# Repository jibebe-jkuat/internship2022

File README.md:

# EV project internship 2022

[PPT Slide](https://docs.google.com/presentation/d/1OYJdxiVj7QEA71lRJihHxvrTG2KooOGciBFLIxmFiqk/edit?usp=sharing)

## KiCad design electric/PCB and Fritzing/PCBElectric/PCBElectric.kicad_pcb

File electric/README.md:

# System Specifications

# MOTOR
Motor: BLDC <BR>
Voltage: 48V <br>
Power rating: 1200W <br>
Serial No: TP48V 1200W H60 210918 0001 <br>

# Speed Controller

Voltage : 48V
Power rating: 1200W

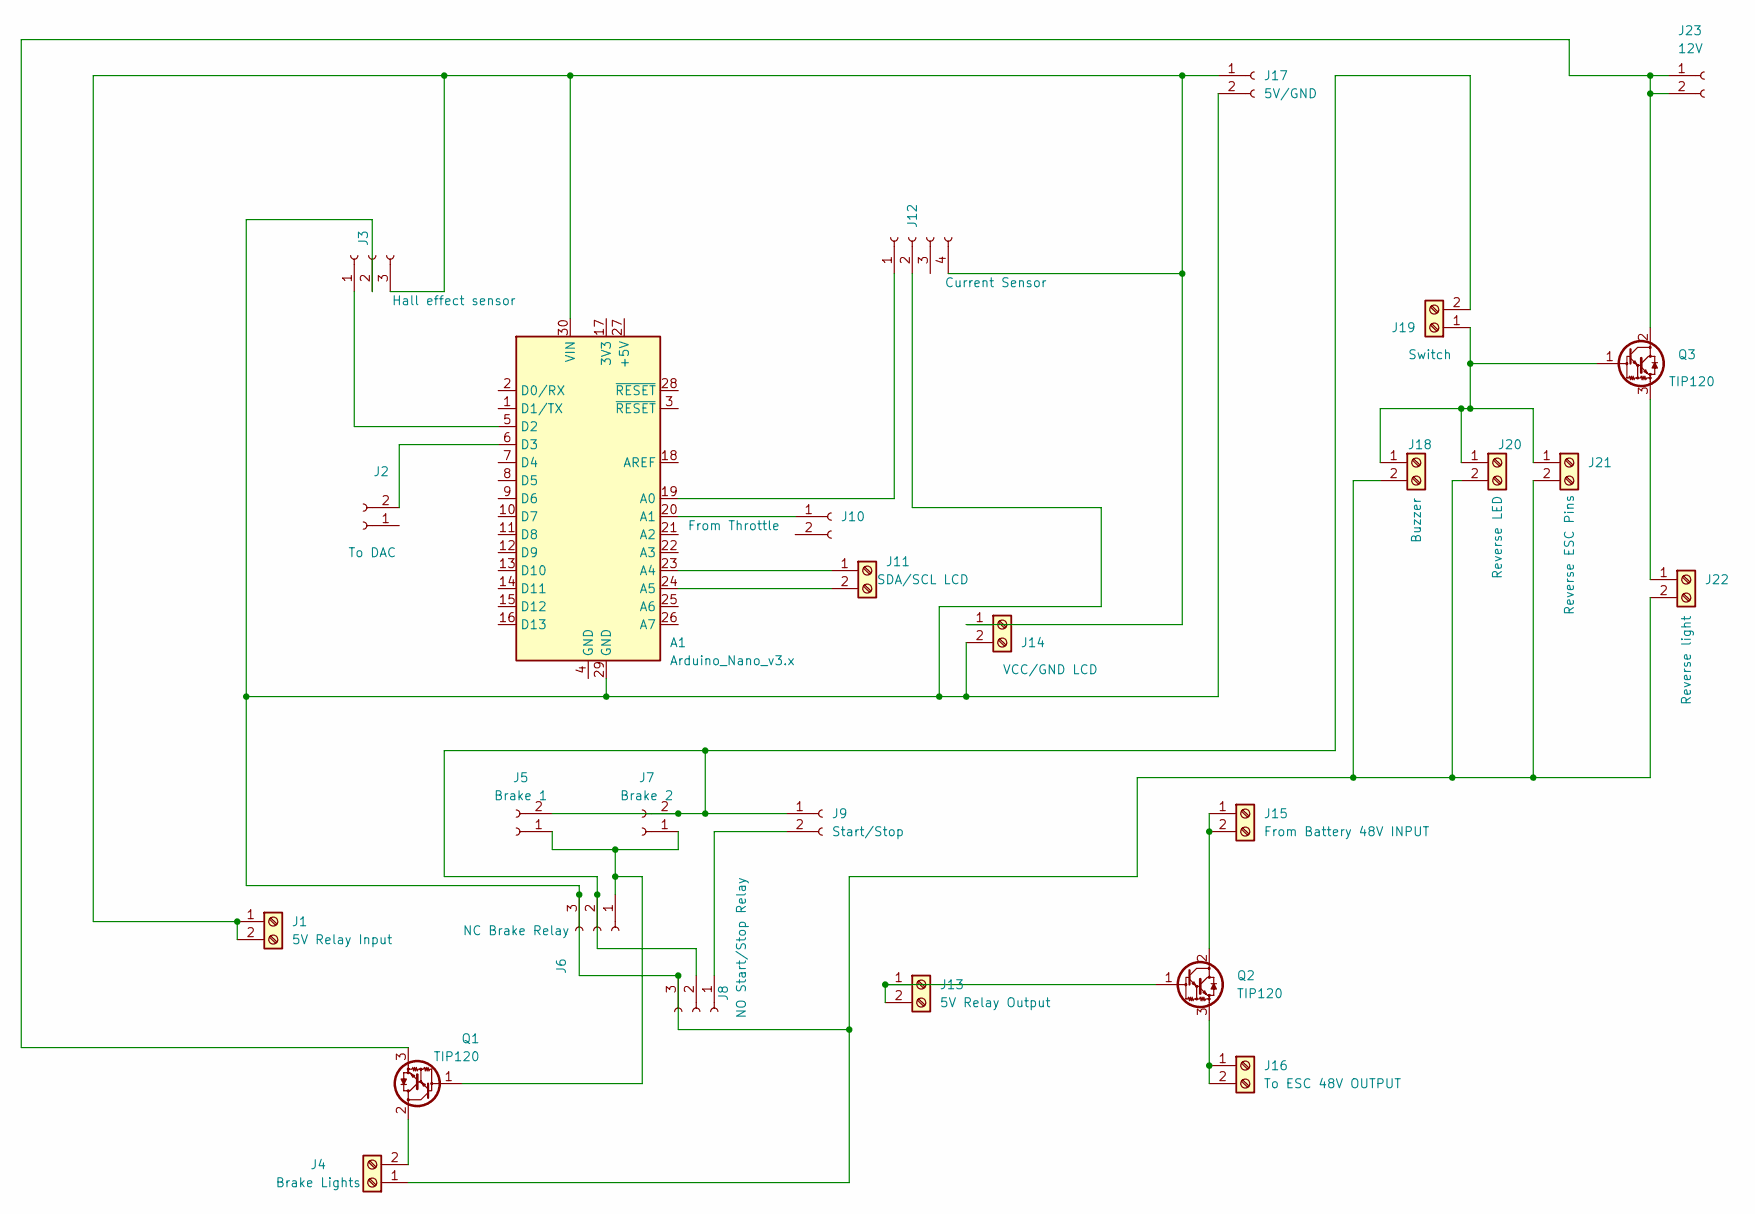
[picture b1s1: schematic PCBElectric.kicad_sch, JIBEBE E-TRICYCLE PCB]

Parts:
A1: Arduino_Nano_v3.x; Arduino_Nano
J1: 5V Relay Input; TerminalBlock_Altech_AK300-2_P5.00mm
J2: To DAC; PinHeader_1x02_P2.54mm_Vertical
J3: Hall effect sensor; PinSocket_1x03_P2.54mm_Vertical
J4: Brake Lights; TerminalBlock_Altech_AK300-2_P5.00mm
J5: Brake 1; PinSocket_1x02_P2.54mm_Vertical
J6: NC Brake Relay; PinSocket_1x03_P2.54mm_Vertical
J7: Brake 2; PinSocket_1x02_P2.54mm_Vertical
J8: NO Start/Stop Relay; PinSocket_1x03_P2.54mm_Vertical
J9: Start/Stop; PinSocket_1x02_P2.54mm_Vertical
J10: From Throttle; PinHeader_1x02_P2.54mm_Vertical
J11: SDA/SCL LCD; TerminalBlock_Altech_AK300-2_P5.00mm
J12: Current Sensor; PinSocket_1x04_P2.54mm_Vertical
J13: 5V Relay Output; TerminalBlock_Altech_AK300-2_P5.00mm
J14: VCC/GND LCD; TerminalBlock_Altech_AK300-2_P5.00mm
J15: From Battery 48V INPUT; TerminalBlock_Altech_AK300-2_P5.00mm
J16: To ESC 48V OUTPUT; TerminalBlock_Altech_AK300-2_P5.00mm
J17: 5V/GND; PinHeader_1x02_P2.54mm_Vertical
J18: Buzzer; TerminalBlock_Altech_AK300-2_P5.00mm
J19: Switch; TerminalBlock_Altech_AK300-2_P5.00mm
J20: Reverse LED; TerminalBlock_Altech_AK300-2_P5.00mm
J21: Reverse ESC Pins; TerminalBlock_Altech_AK300-2_P5.00mm
J22: Reverse light; TerminalBlock_Altech_AK300-2_P5.00mm
J23: 12V; PinHeader_1x02_P2.54mm_Vertical
Q1, Q2, Q3: TIP120; TO-220-3_Vertical

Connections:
unnamed: A1.5 (D2), J3.1
unnamed: A1.6 (D3), J2.2
unnamed: A1.19 (A0), J12.1
unnamed: A1.20 (A1), J10.1
unnamed: A1.23 (A4), J11.1
unnamed: A1.24 (A5), J11.2
unnamed: A1.29 (GND), J3.2, J4.1, J6.3, J8.3, J12.2, J14.2, J17.2, J18.2, J20.2, J21.2, J22.2
unnamed: A1.30 (VIN), J1.1, J1.2, J3.3, J12.4, J14.1, J17.1
unnamed: J4.2, Q1.2 (C)
unnamed: J5.1, J6.1, J7.1, Q1.1 (B)
unnamed: J8.1, J9.2
unnamed: J13.1, J13.2, Q2.1 (B)
unnamed: J15.1, J15.2, Q2.2 (C)
unnamed: J16.1, J16.2, Q2.3 (E)
unnamed: J18.1, J19.1, J20.1, J21.1, Q3.1 (B)
unnamed: J5.2, J6.2, J7.2, J8.2, J9.1, J19.2
unnamed: J22.1, Q3.3 (E)
unnamed: J23.1, J23.2, Q1.3 (E), Q3.2 (C)

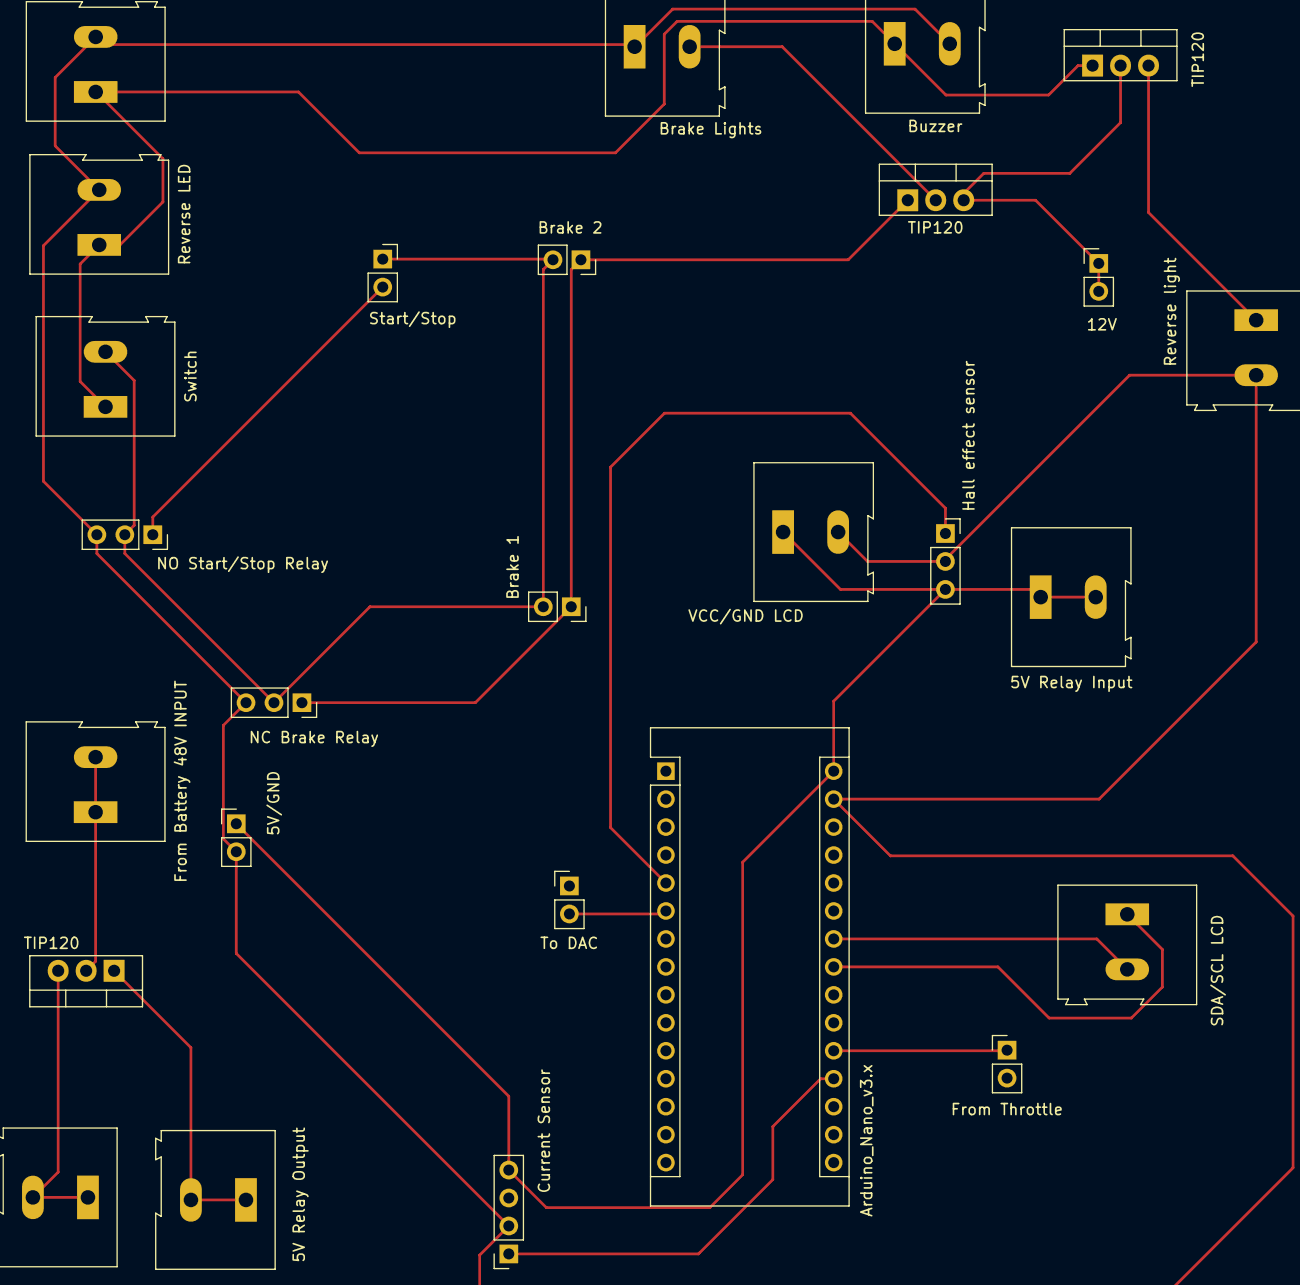
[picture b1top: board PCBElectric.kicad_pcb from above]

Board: 2 copper layers, 27 parts (0 on the bottom side), 18 nets.

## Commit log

2022-01-13 add students
2022-01-13 add introduction slide on readme
2022-01-13 Updated layout of electric team folder
    Different subdirectories have been created to match expected goals
2022-01-14 Uploaded Schematic For Speed Control
2022-01-14 Uploaded README's for the subdirectories
2022-01-16 Uploaded pdf containing choice of battery
2022-01-16 Uploaded code and schematic for speed control
2022-01-17 uploaded battery selection program
2022-01-17 CREATED TXT
2022-01-17 tractor robot chassis
2022-01-17 PARTS USED IN MAKING A OBSTACLE AVOIDING ROBOT CAR
2022-01-17 PARTS USED IN MAKING AN OBSTACLE ROBOT CAR
2022-01-18 uploaded battery and motor sizing calculations
2022-01-19 Updated speed control
    Uploaded images of the suggested handlebar throttle switch
2022-01-19 🚀 RELEASE: Week 1 progress report
2022-01-19 WEEK 1 PROGRESS REPORT
2022-01-19 WEEK 1 report
2022-01-19 progress report
2022-01-21 Add files via upload
    First document describing the choice of battery and motor
2022-01-21 Add files via upload
    Progress report for week 1. Version 1
2022-01-26 Progress report week 1
2022-01-26 🚀 RELEASE: Week 2 progress report
2022-01-26 Week 2 report
2022-01-26 progress report
2022-01-31 ProgressReportWeek2
    Activities done in week 2
2022-02-02 REPORT
2022-02-02 Uploaded reports and Images
2022-02-02 🚀 RELEASE: Week 3 progress report
2022-02-02 uploaded obstacle ultrasonic
2022-02-03 Refactored folder & uploaded GPS
2022-02-07 haversine
2022-02-08 HMC5883L COMPASS
2022-02-08 Refactrored Folders to separate shujaa and tricycle
2022-02-08 🚀 RELEASE: Week 4 progress report
2022-02-09 week 4 progress report
2022-02-11 Add files via upload
    This is a report of the tasks accomplished in week 3.
2022-02-11 Add files via upload
    A report on the activities conducted in week 4
2022-02-14 HMC5883L
2022-02-14 GPS & Compass
2022-02-15 uploaded Resources folder and logo
2022-02-16 uploaded report and GPS code
2022-02-16 3D model
2022-02-17 COMPUTER VISION
2022-02-19 🚀 RELEASE: Week 5 progress report
2022-02-22 Add files via upload
    Week 6 progress report
2022-02-25 Updated graphing
2022-03-01 video capture
2022-03-02 Added more resources
2022-03-02 🚀 RELEASE: Week 7 progress report
2022-03-02 week 7
2022-03-02 week 8 progress report
2022-03-07 rasp berry pi
2022-03-08 TCP/IP
2022-03-08 WEEK 8
2022-03-16 Add files via upload
    Week 9 progress report
2022-03-23 WEEK 10 PROGRESS REPORT
2022-03-23 🚀 RELEASE: Week 10 progress report
2022-03-24 Uploaded acceleration test
2022-03-30 week 11 report
2022-03-31 added speedometer
2022-04-13 week 13 progress report
2022-04-21 LCD Hello World!
2022-04-27 🚀 RELEASE: Week 16 progress report
2022-04-27 week 16
2022-04-29 Create Final code
2022-05-02 Updated final code
2022-05-02 updated lcd
